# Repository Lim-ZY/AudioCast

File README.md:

# AudioCast: Enabling Ubiquitous Connectivity for Embedded Systems through Audio-Broadcasting Low-power Tags

## Overview

Wireless connectivity challenges hinder the deployment of embedded systems. We introduce AudioCast to address two critical issues: spectrum scarcity-induced contention and high power consumption in transmitters. The widespread availability of broadcast radio receivers (for example, FM radios using the 88–108 MHz spectrum) and access to underutilized lower-frequency spectrum motivate the design of AudioCast. The lower-frequency spectrum offers superior radio-wave propagation characteristics, exhibiting at least 10× lower path loss than the 2.4 GHz and 5 GHz Industrial, Scientific, and Medical (ISM) bands while avoiding congestion and interference. These properties enable reliable and long-distance communication, even for weakly radiated signals. AudioCast builds on these properties and the unique negative resistance of a tunnel diode.

AudioCast rethinks the architecture of radio transmitters using a tunnel diode oscillator to generate carrier signals and self-modulate them with baseband signals. This results in frequency-modulated transmissions at an overall power consumption below 200 μW. Unlike related systems based on the backscatter mechanism, AudioCast does not require an externally generated carrier or rely on ambient signals. We argue that AudioCast represents an example of a new class of transmitters which we conceptualize as Beyond-Backscatter transmitters. Through experiments, we demonstrate that AudioCast achieves a transmission range of up to 130 m in line-of-sight and tens of meters in non-line-of-sight conditions respectively. These transmissions are decodable by ubiquitous commodity FM receivers in cars, homes, and phones. We evaluate AudioCast through theoretical analysis, benchtop experiments, and urban/indoor field deployments. Additionally, we prototype and demonstrate novel applications, including low-power voice transmissions and hand gesture communication, enabled by AudioCast’s range and power efficiency.

## Repository Organization

```
├── LICENSE                
├── README.md
├── frequency_scanner         # Utility to scan unallocated FM frequencies
├── hardware                  # PCB hardware design files for baseband generator and frontend
├── assets                    # Images, videos, posters, etc.
└── transmitter_firmware      # Firmware code for baseband generator, FM tuner, etc.
```

## AudioCast System Preview

### FM Modulation vs Mixing

With increasing frequency of baseband / message signal, the value of the modulation index reduces and it becomes narrowband frequency modulation. A narrowband frequency modulation can be approximated as a mixing process, with upper sidebands becoming negligible which is shown in the following video:

https://github.com/user-attachments/assets/ccb81c37-590c-4e0f-b894-82cb153416e6

Alternatively: Watch it [here](https://www.youtube.com/watch?v=7RvvvsP36FI)

### Indoor NLoS Audio Evaluation

Non-line-of-sight (NLoS) evaluation of AudioCast transmitter, showing the transmitted audio snippets and corresponding received audio snippets at 7 different locations. We transmitted audio snippets of 30s but for the video we depict only 5s to make it brief. Furthermore, the calculated PESQ score for evaluating the received audio quality is also shown in the following video:

https://github.com/user-attachments/assets/ebbb9d8d-553b-4ae6-ada7-a8c252bf67cc

Alternatively: Watch it [here](https://www.youtube.com/watch?v=k4Gf5YFvplg)

> The above videos can also be previewed [here](./assets/videos/).

## Publications

1. [**ACM IMWUT (UbiComp) '25**](https://doi.org/10.1145/3729471) - *AudioCast: Enabling Ubiquitous Connectivity for Embedded Systems through Audio-Broadcasting Low-power Tags*
   > **Full paper** to appear in IMWUT - June '25: **Vol. 9, No. 2, Article 27** and to be presented at ACM UbiComp '25 in Espoo, Finland.
    <details>
    <summary>Click to expand citation</summary>

    ```
    @article{audiocast_imwut25,
        author = {Reddy, C. Rajashekar; Shah, Dhairya Jigar; Ang, Nobel and Varshney, Ambuj (to appear)},
        title = {AudioCast: Enabling Ubiquitous Connectivity for Embedded Systems through Audio-Broadcasting Low-power Tags},
        journal = {IMWUT},
        year = {2025},
        issue_date = {June 2025},
        publisher = {Association for Computing Machinery},
        address = {New York, NY, USA},
        volume = {9},
        number = {2},
        url = {https://doi.org/10.1145/3729471},
        doi = {10.1145/3729471},
        articleno = {27},
        numpages = {32},
    }
    ```

    </details>

 2. [**ACM MobiSys '25**](https://www.sigmobile.org/mobisys/2025/) - *Enabling Ubiquitous Connectivity for Embedded Systems through Audio-Broadcasting Low-power Tags*
    > **Demo** to appear at MobiSys '25 in Anaheim, California, US.
    <details>
    <summary>Click to expand citation</summary>

    ```
    @inproceedings{audiocast_mobisys25,
        author = {Reddy, C. Rajashekar and Shah, Dhairya Jigar and Varshney, Ambuj (to appear)},
        title = {Enabling Ubiquitous Connectivity for Embedded Systems through Audio-Broadcasting Low-power Tags},
        year = {2025},
        publisher = {Association for Computing Machinery},
        address = {New York, NY, USA},
        numpages = {2},
        location = {Anaheim, California, US},
        series = {MOBISYS '25}
    }
    ```
    </details>

 3. [**ACM ENSsys '23**](https://dl.acm.org/doi/10.1145/3628353.3628546) - *Beyond Broadcasting: Revisiting FM Frequency-band for Providing Connectivity to Next Billion Devices*
    > **Paper** presented at EnSsys '23 Workshop which has held in conjunction with ACM SenSys '23 in Istanbul, Turkey. AudioCast builds on this early work.
    <details>
    <summary>Click to expand citation</summary>
    
    ```
    @inproceedings{tunnelradio_enssys23,
        author = {Reddy, C. Rajashekar and Gulati, Manoj and Varshney, Ambuj},
        title = {Beyond Broadcasting: Revisiting FM Frequency-band for Providing Connectivity to Next Billion Devices},
        year = {2023},
        isbn = {9798400704383},
        publisher = {Association for Computing Machinery},
        address = {New York, NY, USA},
        url = {https://doi.org/10.1145/3628353.3628546},
        doi = {10.1145/3628353.3628546},
        booktitle = {Proceedings of the 11th International Workshop on Energy Harvesting \& Energy-Neutral Sensing Systems},
        pages = {30–36},
        numpages = {7},
        keywords = {FM communication, Internet of Things (IoT), Low-Power Communication, Tunnel Diodes},
        location = {Istanbul, Turkiye},
        series = {ENSsys '23}
    }
    ```

## Contributors and Team

AudioCast is developed and maintained by the following researchers from the [WEISER group](https://weiserlab.github.io/ambuj/) from the School of Computing, National University of Singapore (NUS). 

1. [C. Rajashekar Reddy](https://github.com/rez39)
2. [Dhairya Shah](https://github.com/dhairyashah1/)
3. [Prof. Ambuj Varshney](https://github.com/weiserlab/)

> Feel free to contact us at [`rajashekar.c@u.nus.edu`](mailto:rajashekar.c@u.nus.edu) or [`dhairya@u.nus.edu`](mailto:dhairya@u.nus.edu) for any questions or suggestions.

## Acknowledgements

We acknowledge Nobel Ang, [Yuvraj Singh Bhadauria](https://github.com/UvrajSB) and [Manoj Gulati](https://github.com/manojgulati) for their assistance and support during the early stages of this work.

## Funding

This research is fully supported by the Advanced Research and Technology Innovation Centre **(ARTIC)** at the National University of Singapore. In addition, some parts of this work are supported by a **Tier 1 grant** from Ministry of Education. It is also supported by a **Startup Grant** from ODPRT and an unrestricted gift from Google through their **Research Scholar Program**, all of which are hosted at the National University of Singapore (NUS).

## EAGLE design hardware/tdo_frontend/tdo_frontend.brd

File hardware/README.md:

# Hardware Design Files

This folder contains PCB design files for the hardware: baseband generator and tunnel-diode oscillator frontend (TDO) used in AudioCast.

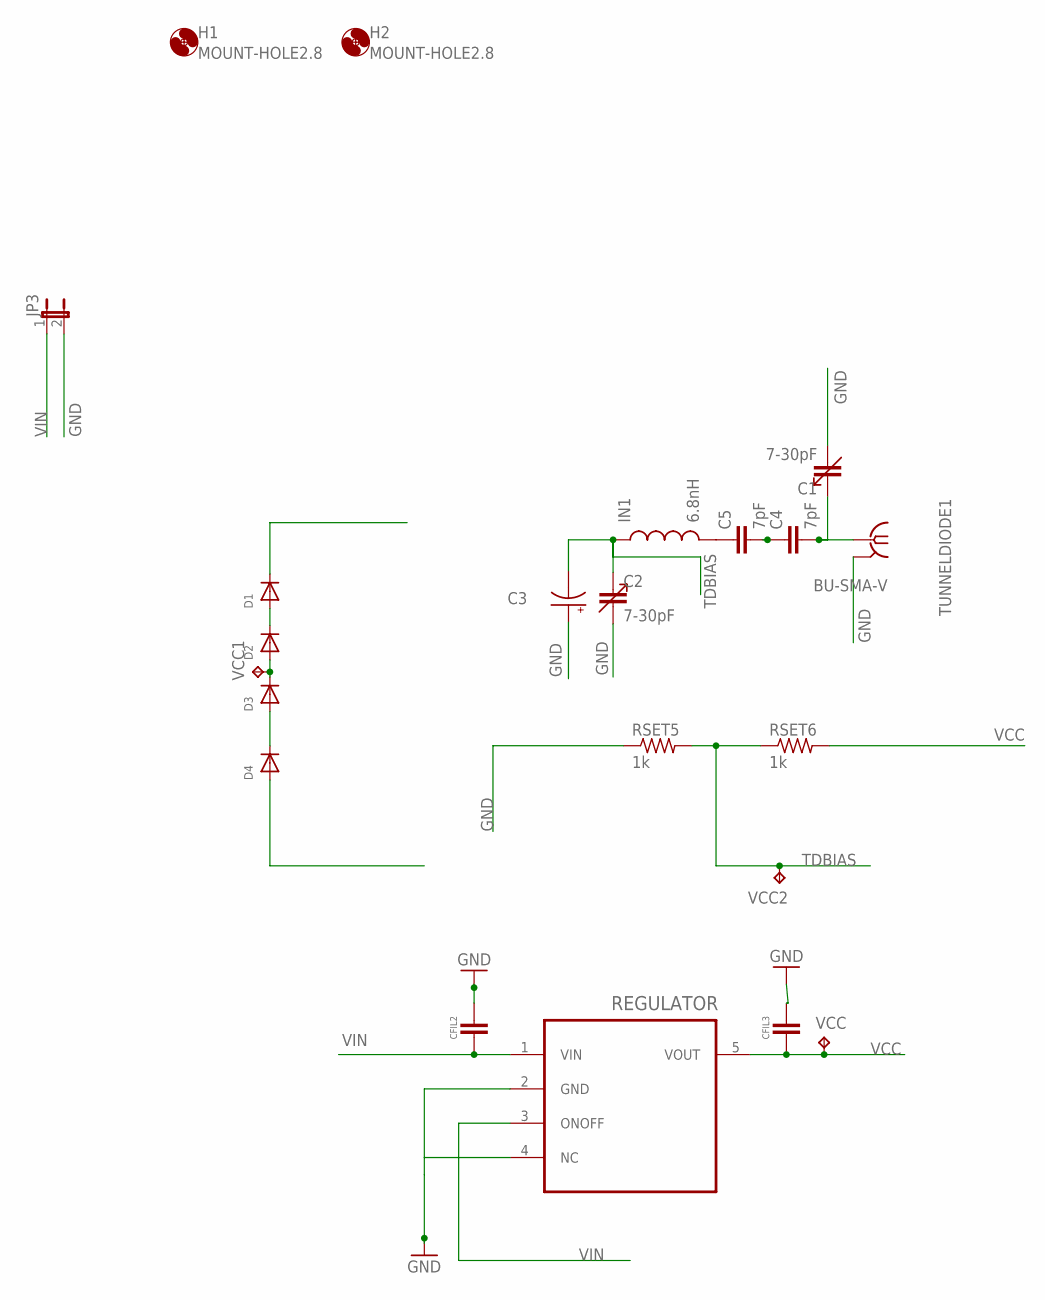
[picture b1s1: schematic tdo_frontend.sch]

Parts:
C1, C2: 7-30pF; CTZ3
C3: .22F-SUPERCAP; DSK-RADIAL-4.8MM
C4, C5: 7pF; C0603
CFIL2, CFIL3: 0805_1; 0805_1PRIMARY
D1, D2, D3, D4: DIODEDO-1N4148; DO-1N4148
H1, H2: MOUNT-HOLE2.8; 2,8
IN1: 6.8nH; 0603_1PRIMARY
JP3: JP1E; JP1
REGULATOR: S-1313B20; SOT23-5
RSET5, RSET6: 1k; R0603
TUNNELDIODE1: BU-SMA-V
VCC, VCC1, VCC2: TPPAD1-17; P1-17

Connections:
ANT2: C1.+ (3), C4.2, TUNNELDIODE1.1
GND: C1.- (4), C2.- (4), C3.+, CFIL2.2, CFIL3.2, JP3.2, REGULATOR.2 (GND), REGULATOR.4 (NC), RSET5.1, TUNNELDIODE1.2, TUNNELDIODE1.3 (2), TUNNELDIODE1.4 (2), TUNNELDIODE1.5 (2)
unnamed: D3.A, D4.C
unnamed: C4.1, C5.2
unnamed: D2.A, D3.C, VCC1.TP
unnamed: C5.1, IN1.2
unnamed: D1.A, D2.C
TDBIAS: C2.+ (3), C3.-, IN1.1, RSET5.2, RSET6.1, VCC2.TP
VCC: CFIL3.1, REGULATOR.5 (VOUT), RSET6.2, VCC.TP
VIN: CFIL2.1, JP3.1, REGULATOR.1 (VIN), REGULATOR.3 (ONOFF)

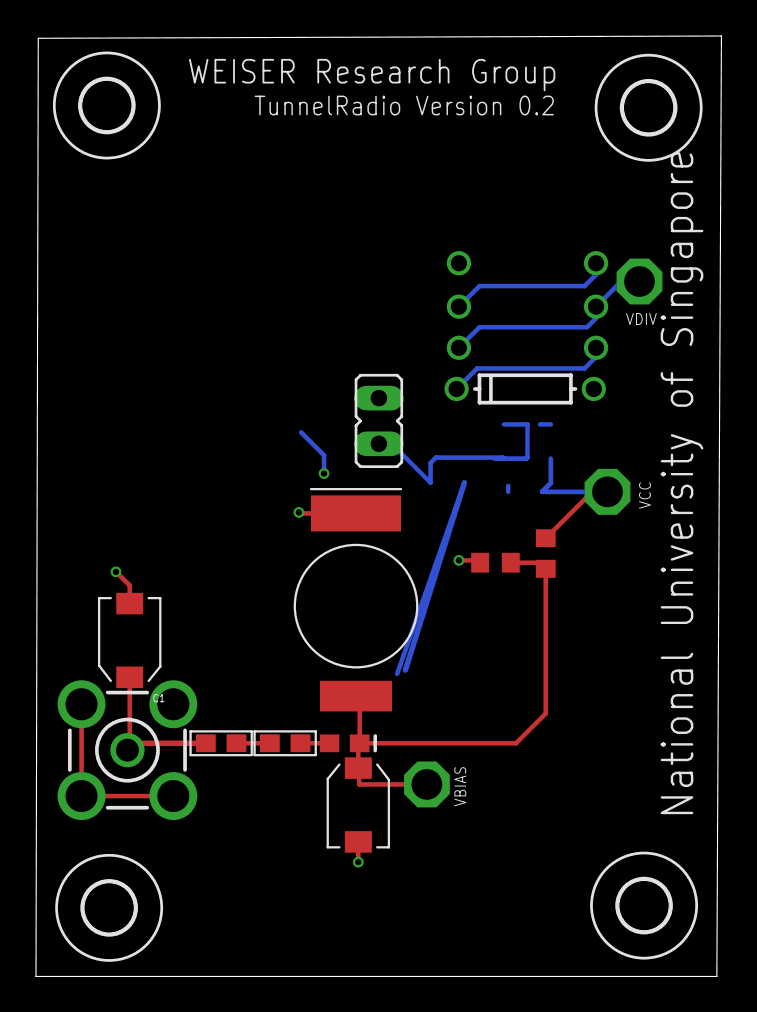
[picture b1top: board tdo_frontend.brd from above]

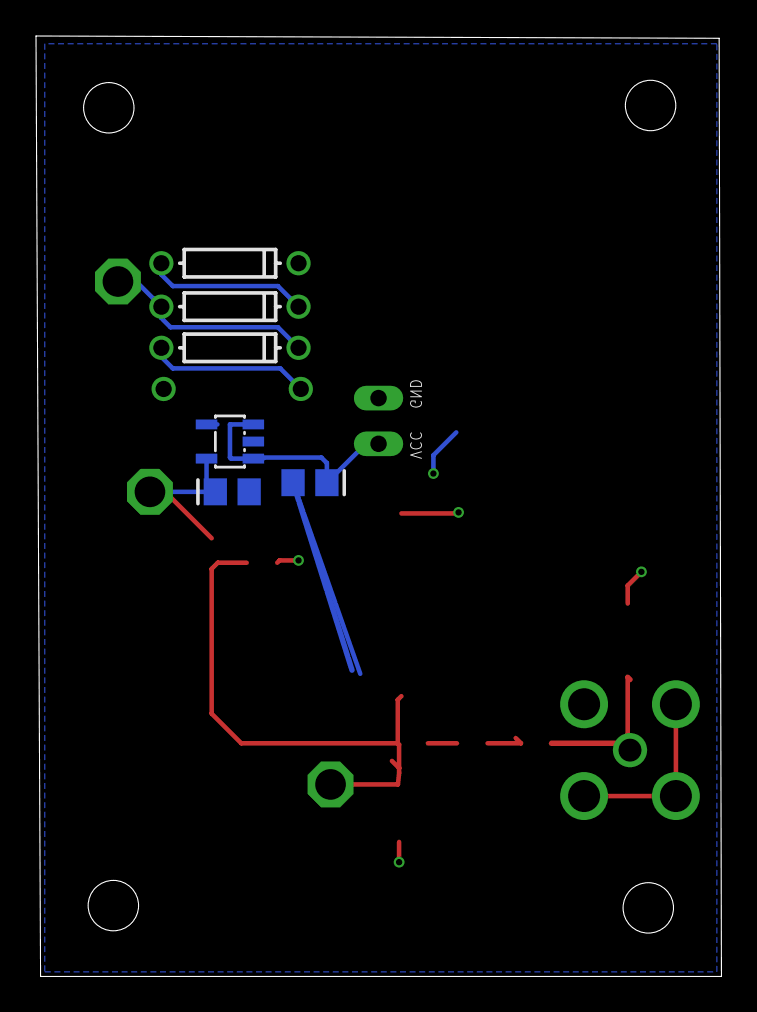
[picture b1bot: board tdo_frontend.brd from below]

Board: 2 copper layers, 38.1 x 52.2 mm, 24 parts (6 on the bottom side), 10 nets.

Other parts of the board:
H3, H4: MOUNT-HOLE2.8; 2,8

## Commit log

2025-04-20 Adds hardware design files, ESP32 firmware and FM whitespace scanner
2025-04-20 Minor changes
2025-04-21 Adds demo videos for FM modulation -> mixing and indoor PESQ
2025-04-21 Adds video previews:
2025-04-21 Fixed video previews in README.md
2025-04-22 Adds publications and details to README.md
2025-04-22 Minor changes to publication links
2025-06-13 Working first implementation
2025-06-24 Working TX with updated delay per ms
2025-07-30 first push
2025-07-31 Final working implementation with I2C
2025-07-31 Create README.md
    Connections from MSP430 to SI4713 (connect RST of SI4713 to RST of MSP430 instead)
2025-08-07 Update README for MSP430

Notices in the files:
parts and their libraries:
SparkFun-Capacitors: Licensing: CC v3.0 Share-Alike You are welcome to use this library for commercial purposes.
SparkFun-Capacitors: Licensing: Creative Commons ShareAlike 4.0 International - https://creativecommons.org/licenses/by-sa/4.0
